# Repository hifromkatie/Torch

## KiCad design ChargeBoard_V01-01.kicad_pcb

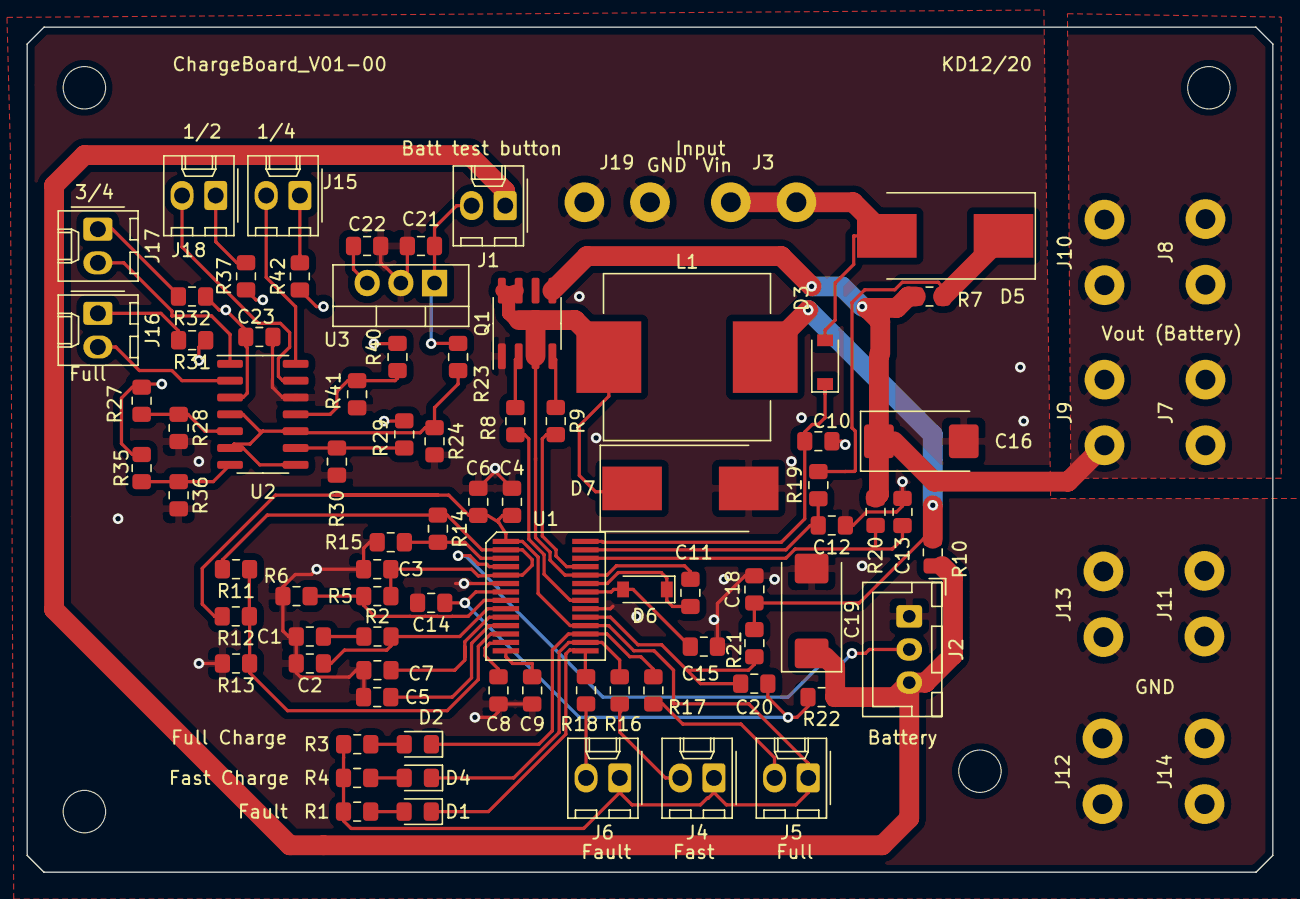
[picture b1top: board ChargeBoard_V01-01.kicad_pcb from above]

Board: 2 copper layers, 94.0 x 63.8 mm, 93 parts (0 on the bottom side), 54 nets.

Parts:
C1, C6, C10, C11, C12, C13, C15, C22, C23: 0.1u; C_0805_2012Metric_Pad1.15x1.40mm_HandSolder
C2, C8, C9, C14, C18, C20: 1n; C_0805_2012Metric_Pad1.15x1.40mm_HandSolder
C3: 1u; C_0805_2012Metric_Pad1.15x1.40mm_HandSolder
C4: 4.7u; C_0805_2012Metric_Pad1.15x1.40mm_HandSolder
C5, C7: 47n; C_0805_2012Metric_Pad1.15x1.40mm_HandSolder
C16: 22u; CP_EIA-7343-15_Kemet-W_Pad2.25x2.55mm_HandSolder
C19: 68u; CP_EIA-7343-30_AVX-N_Pad2.25x2.55mm_HandSolder
C21: 0.33u; C_0805_2012Metric_Pad1.15x1.40mm_HandSolder
D1, D2, D4: LED; LED_0805_2012Metric_Pad1.15x1.40mm_HandSolder
D3, D6: D; D_SOD-123
D5, D7: D_Schottky; D_SMC_Handsoldering
H1, H2, H3, H4: MountingHole; MountingHole_3.2mm_M3
J1, J4, J5, J6, J15, J16, J17, J18: Conn_01x02_Female; Molex_KK-254_AE-6410-02A_1x02_P2.54mm_Vertical
J2: Conn_01x03_Male; JST_XH_B3B-XH-A_1x03_P2.50mm_Vertical
J3, J7, J8, J9, J10, J11, J12, J13, J14, J19: Conn_01x01_Female; Faston250
L1: 22u; L_Wuerth_WE-PD-Typ-LS_Handsoldering
Q1: FDS6990A; SOIC-8_3.9x4.9mm_P1.27mm
R1, R3, R4, R16, R17, R18, R24, R31, R32, R37, R42: 1k; R_0805_2012Metric_Pad1.15x1.40mm_HandSolder
R2: 10k; R_0805_2012Metric_Pad1.15x1.40mm_HandSolder
R5, R6, R14, R36: 100k; R_0805_2012Metric_Pad1.15x1.40mm_HandSolder
R7: 0.05; R_0805_2012Metric_Pad1.15x1.40mm_HandSolder
R8, R9: 10; R_0805_2012Metric_Pad1.15x1.40mm_HandSolder
R10: 0.1 1%; R_0805_2012Metric_Pad1.15x1.40mm_HandSolder
R11, R13: DNF; R_0805_2012Metric_Pad1.15x1.40mm_HandSolder
R12: 0; R_0805_2012Metric_Pad1.15x1.40mm_HandSolder
R15: 300k; R_0805_2012Metric_Pad1.15x1.40mm_HandSolder
R19, R20, R21, R22: 4.7; R_0805_2012Metric_Pad1.15x1.40mm_HandSolder
R23: 3k; R_0805_2012Metric_Pad1.15x1.40mm_HandSolder
R27: 16k; R_0805_2012Metric_Pad1.15x1.40mm_HandSolder
R28, R41: 51k; R_0805_2012Metric_Pad1.15x1.40mm_HandSolder
R29: 62k; R_0805_2012Metric_Pad1.15x1.40mm_HandSolder
R30: 110k; R_0805_2012Metric_Pad1.15x1.40mm_HandSolder
R35: 39k; R_0805_2012Metric_Pad1.15x1.40mm_HandSolder
R40: 24k; R_0805_2012Metric_Pad1.15x1.40mm_HandSolder
U1: MAX1737; QSOP-28
U2: LM2901; SOIC-14_3.9x8.7mm_P1.27mm
U3: L7805; TO-220-3_Vertical

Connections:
+5V: C22.1, C23.1, R27.1, R29.1, R31.1, R32.1, R35.1, R37.1, R40.1, R42.1, U2.3, U3.3
+BATT: C19.1, J1.1, J2.3, R10.1, R22.1
/Battery Level display/CheckBat: C21.1, J1.2, R23.1, U3.1
/Battery Level display/QBat: R23.2, R24.1, U2.4, U2.6, U2.8, U2.10
GND: C1.2, C2.2, C3.1, C4.1, C5.1, C6.1, C7.1, C8.1, C9.1, C10.1, C12.1, C13.1, C14.2, C15.1, C16.2, C18.2, C19.2, C21.2, C22.2, C23.2, D7.2, J2.1, J11.1, J12.1, J13.1, J14.1, J19.1, Q1.1, R6.2, R13.2, R15.2, R24.2, R28.2, R30.2, R36.2, R41.2, U1.6, U1.20, U2.12, U3.2
unnamed: C1.1, R2.2
unnamed: C2.1, R2.1, U1.9
unnamed: C3.2, R5.1, R11.2, R14.1, U1.2, U1.5
unnamed: C4.2, C6.2, J4.1, J5.1, J6.1, R1.1, R3.1, R4.1, R12.2, U1.1, U1.18
unnamed: C5.2, U1.11
unnamed: C7.2, U1.10
unnamed: C8.2, U1.13
unnamed: C9.2, U1.14
unnamed: C10.2, D3.1, U1.28
unnamed: C11.1, D6.1, U1.23
unnamed: C11.2, D7.1, L1.1, Q1.3, Q1.7, Q1.8, U1.24
unnamed: C12.2, R19.2, U1.27
unnamed: C13.2, R20.2, U1.26
unnamed: C14.1, C20.2, R22.2, U1.7
unnamed: C15.2, D6.2, U1.22
unnamed: C16.1, J7.1, J8.1, J9.1, J10.1, Q1.5, Q1.6, R7.1, R20.1
unnamed: C18.1, L1.2, R10.2, R21.1
unnamed: C20.1, R21.2, U1.19
unnamed: D1.1, R18.1, U1.15
unnamed: D1.2, R1.2
unnamed: D2.1, R17.1, U1.17
unnamed: D2.2, R3.2
unnamed: D3.2, D5.2, J3.1
unnamed: D4.1, R16.1, U1.16
unnamed: D4.2, R4.2
unnamed: D5.1, R7.2, R19.1
unnamed: J2.2, U1.4
unnamed: J4.2, R16.2
unnamed: J5.2, R17.2
unnamed: J6.2, R18.2
unnamed: J15.1, R42.2
unnamed: J15.2, U2.14
unnamed: J16.1, R31.2
unnamed: J16.2, U2.2
unnamed: J17.1, R32.2
unnamed: J17.2, U2.1
unnamed: J18.1, R37.2
unnamed: J18.2, U2.13
unnamed: Q1.2, R8.1
unnamed: Q1.4, R9.1
unnamed: R5.2, R6.1, U1.8
unnamed: R8.2, U1.21
unnamed: R9.2, U1.25
unnamed: R11.1, R12.1, R13.1, U1.12
unnamed: R14.2, R15.1, U1.3
unnamed: R27.2, R28.1, U2.5
unnamed: R29.2, R30.1, U2.9
unnamed: R35.2, R36.1, U2.7
unnamed: R40.2, R41.1, U2.11
